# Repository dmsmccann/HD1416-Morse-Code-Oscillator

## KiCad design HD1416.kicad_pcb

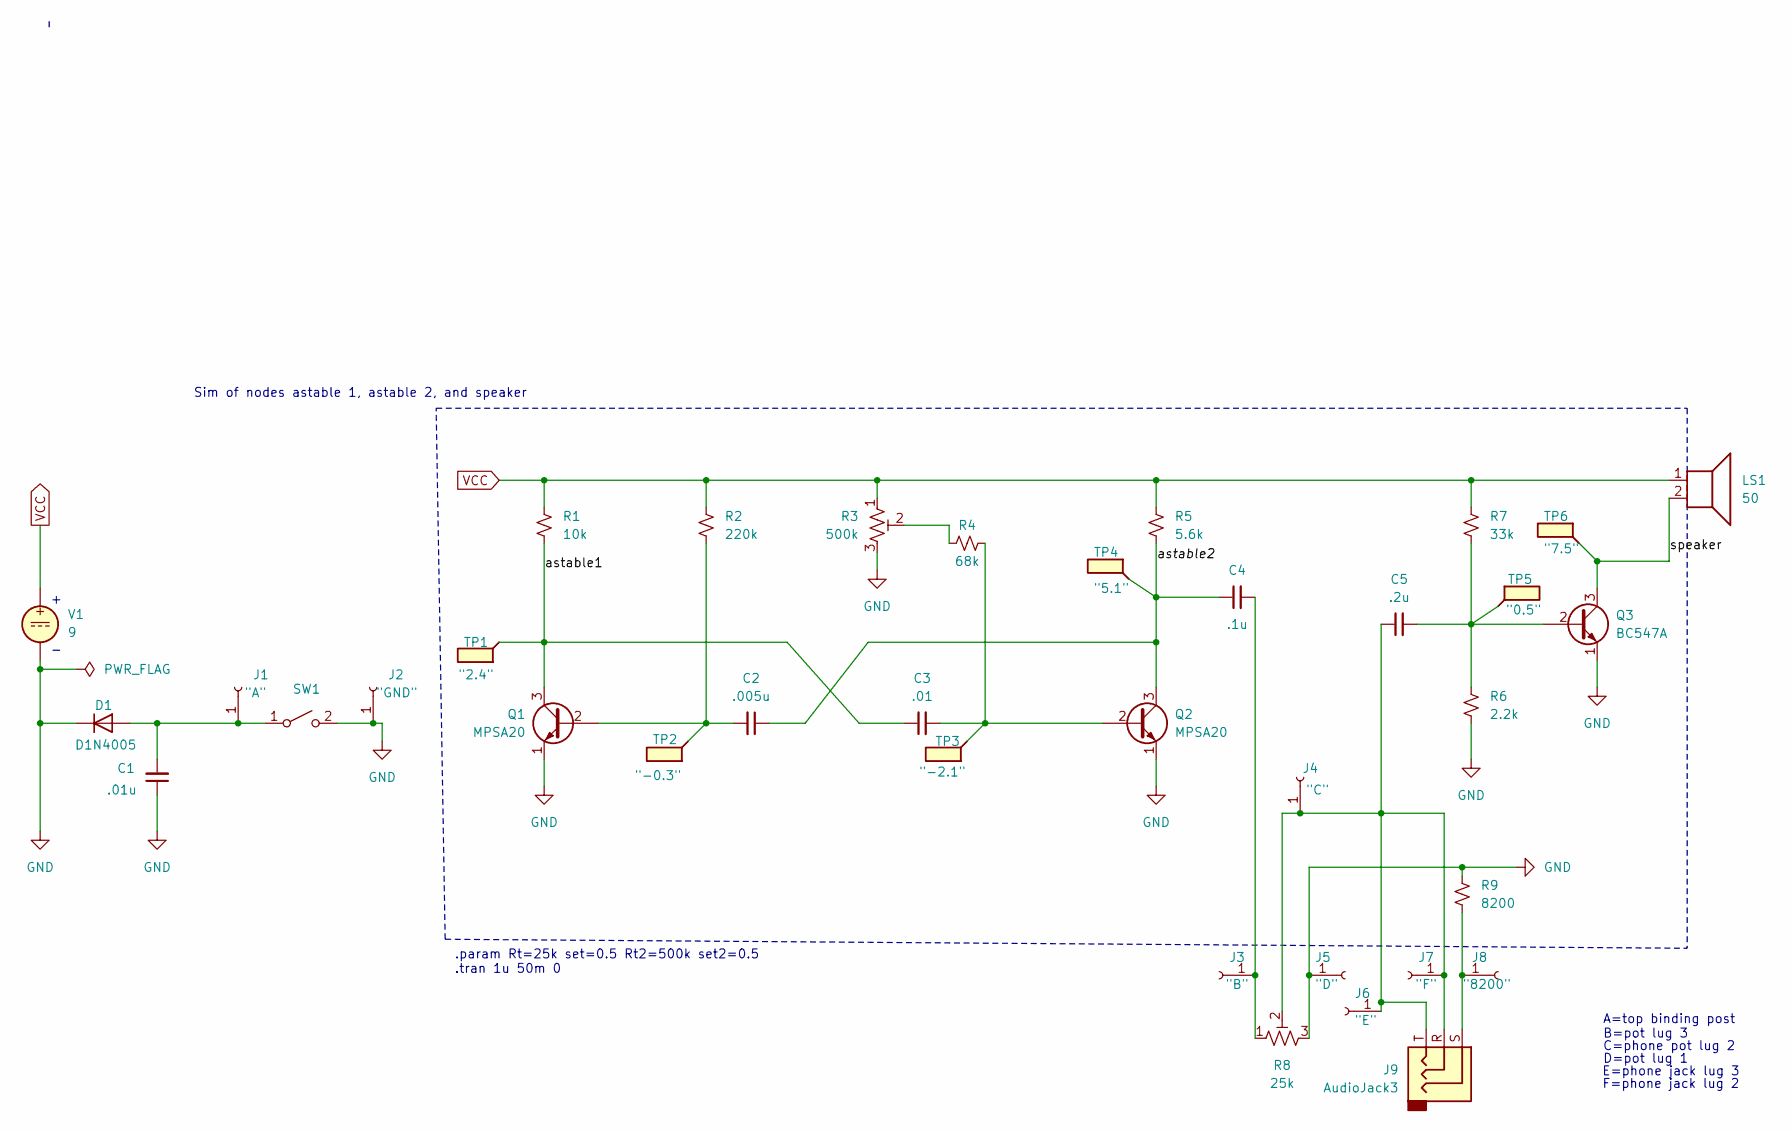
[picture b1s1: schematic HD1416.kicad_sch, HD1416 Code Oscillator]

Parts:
C1: .01u; C_Disc_D3.8mm_W2.6mm_P2.50mm
C2: .005u; C315C103K5R5TA7303
C3: .01; C_Disc_D3.8mm_W2.6mm_P2.50mm
C4: .1u; C_Disc_D3.8mm_W2.6mm_P2.50mm
C5: .2u; C_Disc_D3.8mm_W2.6mm_P2.50mm
D1: D1N4005; D_DO-41_SOD81_P10.16mm_Horizontal
J1: "A"; SolderWire-0.5sqmm_1x01_D0.9mm_OD2.3mm
J2: "GND"; SolderWire-0.5sqmm_1x01_D0.9mm_OD2.3mm
J3: "B"; SolderWire-0.5sqmm_1x01_D0.9mm_OD2.3mm
J4: "C"; SolderWire-0.5sqmm_1x01_D0.9mm_OD2.3mm
J5: "D"; SolderWire-0.5sqmm_1x01_D0.9mm_OD2.3mm
J6: "E"; SolderWire-0.5sqmm_1x01_D0.9mm_OD2.3mm
J7: "F"; SolderWire-0.5sqmm_1x01_D0.9mm_OD2.3mm
J8: "8200"; SolderWire-0.5sqmm_1x01_D0.9mm_OD2.3mm
J9: AudioJack3
LS1: 50; SolderWire-0.5sqmm_1x02_P4.8mm_D0.9mm_OD2.3mm
Q1, Q2: MPSA20; TO-92
Q3: BC547A; TO-92
R1: 10k; CFM12JT10K0
R2: 220k; SFR16S0002203FR500
R3: 500k; 3299X-1-504LF
R4: 68k; CFR-50JB-52-68K
R5: 5.6k; CFR-50JB-52-5K6
R6: 2.2k; CFM12JT2K20
R7: 33k; CFM12JT33K0
R8: 25k
R9: 8200; CF12JT8K20
SW1: type="R" model="SW_SPST" lib=""; SolderWire-0.75sqmm_1x02_P4.8mm_D1.25mm_OD2.3mm
TP1: "2.4"; TestPoint_Pad_D2.0mm
TP2: "-0.3"; TestPoint_Pad_D2.0mm
TP3: "-2.1"; TestPoint_Pad_D2.0mm
TP4: "5.1"; TestPoint_Pad_D2.0mm
TP5: "0.5"; TestPoint_Pad_D2.0mm
TP6: "7.5"; TestPoint_Pad_D2.0mm
V1: 9; BatteryHolder_MPD_BA9VPC_1xPP3 dem

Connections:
/astable1: C3.1, Q1.3 (C), R1.2, TP1.1
/astable2: C2.1, C4.1, Q2.3 (C), R5.2, TP4.1
/speaker: LS1.2, Q3.3 (C), TP6.1
GND: C1.1, D1.1 (K), J2.1, J5.1, Q1.1 (E), Q2.1 (E), Q3.1 (E), R3.3, R6.2, R8.3, R9.1, SW1.2 (B), V1.2
unnamed: C1.2, D1.2 (A), J1.1, SW1.1 (A)
unnamed: C4.2, J3.1, R8.1
unnamed: C5.1, J4.1, J6.1, J7.1, J9.R, J9.T, R8.2
unnamed: J8.1, J9.S, R9.2
unnamed: C2.2, Q1.2 (B), R2.2, TP2.1
unnamed: C3.2, Q2.2 (B), R4.2, TP3.1
unnamed: C5.2, Q3.2 (B), R6.1, R7.2, TP5.1
unnamed: R3.2, R4.1
VCC: LS1.1, R1.1, R2.1, R3.1, R5.1, R7.1, V1.1

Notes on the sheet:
D=pot lug 1
.param Rt=25k set=0.5 Rt2=500k set2=0.5 .tran 1u 50m 0
Sim of nodes astable 1, astable 2, and speaker
C=phone pot lug 2
E=phone jack lug 3
A=top binding post
F=phone jack lug 2
B=pot lug 3

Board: 2 copper layers, 33 parts (0 on the bottom side), 13 nets, no tracks yet.

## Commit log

2022-05-09 first part placement on PCB
2022-05-10 Updates to PCBNew
2022-05-10 corrected pcb and sch
2022-05-10 adding the backups
2022-05-10 Fixed pcb new and sch
2022-05-11 routing board and improving 3D
2022-05-12 improved sch pcb 3d
2022-05-12 improved sch and pcb and 3d
2022-05-12 updated modeling
2022-05-30 catching up on all changes
2022-06-21 minor updates
2025-01-04 updates to kicad 8.0
2025-01-04 updates to schematic
2025-01-04 updates to audio jack
2025-01-05 update gitignore
2025-01-05 minor
2025-01-05 changes to folder organization
2025-01-12 minor change

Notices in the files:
parts and their libraries:
Copyright 2021 Accelerated Designs. All rights reserved.
